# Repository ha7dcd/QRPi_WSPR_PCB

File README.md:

# QRPi – Whispering Raspberries: a Raspberry Pi QRP TX shield (20 m WSPR)

QRPi is a 20 m band, 20 dBm RF signal conditioner shield for the Raspberry Pi. It takes the RF square wave that the Pi generates on a GPIO pin and turns it into a clean, filtered QRP transmit signal: a MOSFET (MMBF170) stage followed by a multi-section low-pass filter. It was presented as a TAPR-DCC 2015 talk paper and was sold through TAPR and on Amazon.

This repository holds the board's original EAGLE design and manufacturing files (rev 1.6), and a KiCad 10 version of the same design.

*An earlier prototype (rev 1.1) on a Raspberry Pi model B, with a coax pigtail on the antenna terminal.*

## About the project (from [rfsparkling.com/qrpi](https://rfsparkling.com/qrpi/))

**QRPi - A Raspberry Pi QRP TX Shield Design, TAPR-DCC Talk paper 2015** ([PDF in this repo](docs/DCC2015-QRPI-HA7DCD.pdf))

QRPi is an RF signal conditioner shield for Raspberry Pi. Sourcing the RaspberryPi generated RF signal from GPIO4.

Right now existing only for the **20m band** for **14.0971 MHz** Later on will designed for other bands as well (10m in prototype).

In default GPIO4 mode can be used with [WsprryPi](https://github.com/JamesP6000/WsprryPi), [SSTV](https://github.com/JennyList/LanguageSpy/tree/master/RaspberryPi/rf/sstv), [CW](https://github.com/JamesP6000/PiCW), check manual here: [j.mp/tapr-qrpi](http://j.mp/tapr-qrpi) GPIO4 mode works with RPi 1 B, B+ and RPi 2 as well for WSPR mode.
When using in the **experimental GPIO18** mode (solder jumper selectable; SSB USB, LSB, NFM, WFM, AM with [qtcsdr](https://github.com/ha7ilm/qtcsdr) and [rpitx](https://github.com/F5OEO/rpitx)) it works only with RPi 2 right now (due to CPU demand)

However please be aware that QRPi was engineered and tested for GPIO4 pin, using WSPR modulation!
I'm adding GPIO18 option for **experimental mode only** to use with [qtcsdr](https://github.com/ha7ilm/qtcsdr) and [rpitx](https://github.com/F5OEO/rpitx)! By default the solder jumper is set for GPIO4 by short cut. As for VFO operation (CW signal) GPIO18 works nice but not yet tested comprehensively for other modulation yet, **please take care of this** in shake of RF spectrum emission! The QRPi shield is available at TAPR's webshop: <https://www.tapr.org/kits_20M-wspr-pi.html>

Now available at Amazon too: <https://www.amazon.com/Raspberry-QRP-Sheild-WSPR-Meters/dp/B01FWFKN40/>

Thanks for your interest!

73,
HA7DCD

Video: <https://www.youtube.com/watch?v=w-OTpw2Ai0k>

## The board in 3D (KiCad 10)

| Top | Bottom |
|---|---|
|  |  |

Two-layer board. The Raspberry Pi GPIO header pins pass through the board and into a 2x7 SMD female socket on the top side. The antenna is connected to a 2-pole Phoenix MPT 0,5/2-2,54 screw terminal. The GPIO4 / GPIO18 drive is selected on the bottom side: GPIO4 is shorted by default.

## Repository contents

| Path | What it is |
|---|---|
| `Eagle/20m_QRPi_1V6.sch`, `Eagle/20m_QRPi_1V6.brd` | Original EAGLE schematic and board (EAGLE 6.4 XML format) |
| `Eagle/20m_QRPi_1V6_sch.pdf`, `_top.pdf`, `_bot.pdf` | Schematic and board prints |
| `Eagle/20m_RPI_WSPR_TX_BOM_SMDmount.xlsx` | Bill of materials (SMD assembly) |
| `Eagle/CAM/20m_RPI_WSPR_TX_1v6.zip` | Original manufacturing files: Gerbers, Excellon drill files, PDFs |
| `KiCad/` | KiCad 10 project: schematic, PCB, project symbol and footprint libraries, design rules |
| `KiCad/3dmodels/` | STEP models used by the 3D view, from the KiCad standard library |
| `docs/` | TAPR-DCC 2015 paper, prototype photo, 3D renders, banner |

## About the KiCad version

The KiCad project was converted from the EAGLE files with [Eagle Exhumer](https://github.com/z2labs/eagle-exhumer) and then checked against the EAGLE source and the original manufacturing files:

- Netlist of the schematic and of the board: identical to EAGLE (no shorts, no opens, no renamed nets)
- 33 parts, 78 pads, 169 holes, 144 vias: same position, side, rotation, value, size and drill as in EAGLE
- KiCad-generated Gerbers and drill files compared with the original EAGLE manufacturing files: copper (outside the polygon pours), solder mask, paste and all 169 drill holes match. Polygon pour fill differs by about 2.5 % because EAGLE and KiCad use different fill algorithms.
- Remaining DRC items are the same ones the original EAGLE design carries: the JP1 GPIO4/GPIO18 jumper's solder-mask opening intentionally exposes the GPIO4 track and ground.

Only the EAGLE drawing frame was removed (KiCad draws its own page frame). 3D models were added for 30 of 33 footprints; the solder jumpers JP1 and SJ1 and the OSHW logo have none.

## License

Copyright 2015 Zoltan Doczi - HA7DCD. The hardware design is licensed under the TAPR Open Hardware License (<http://tapr.org/OHL>).

The STEP models in `KiCad/3dmodels/` come from the KiCad library (CC-BY-SA 4.0 with an exception that allows their use in designs, see <https://www.kicad.org/libraries/license/>).

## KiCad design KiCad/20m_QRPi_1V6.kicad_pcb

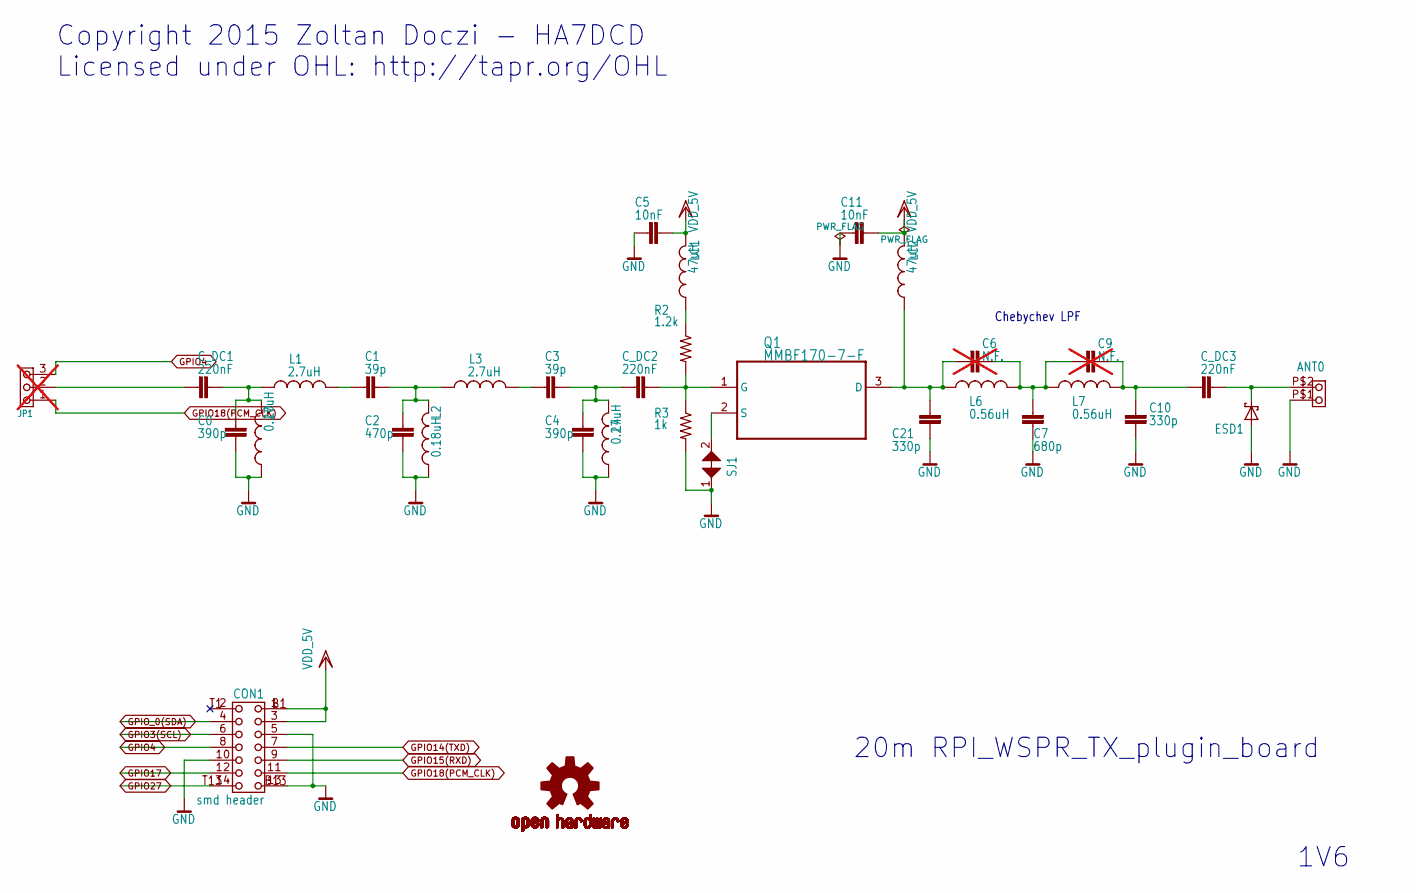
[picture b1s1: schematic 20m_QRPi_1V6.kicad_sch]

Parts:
ANT0: TERMINAL_WIRE_2P_17256562P; WIRE_CONTACT_2P
C0, C4: 390p; 0603
C1, C3: 39p; 0603
C2: 470p; 0603
C5, C11: 10nF; 0603
C6, C9: N.F.; 0603; not fitted
C7: 680p; 0603
C10, C21: 330p; 0603
CON1: smd header; 2X7-SMT_CROSSPCB_ASSYM_DUMY26HOLES
C_DC1, C_DC2, C_DC3: 220nF; 0603
ESD1: PGB1010603NRHF; 0603__v2
JP1: N.F.; PIN3-B_SHORT23; not fitted
L0, L4: 0.27uH; L1210
L1, L3: 2.7uH; L1210
L2: 0.18uH; L1210
L6, L7: 0.56uH; L1210
LC1, LC2: 47uH; L1210
Q1: MMBF170-7-F; SOT103P240X110-3N
R2: 1.2k; R0402
R3: 1k; R0402
SJ1: JUMPER_SMD_MICRO_SHORT
U$15: OSHW-LOGOS; OSHW-LOGO-S

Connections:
GND: ANT0.P$1 (A), C0.1, C2.1, C4.1, C5.2, C7.1, C10.1, C11.2, C21.1, CON1.5, CON1.10, CON1.13, ESD1.1 (A), L0.1, L2.1, L4.1, R3.2, SJ1.1
GPIO3(SCL): CON1.6
GPIO4: CON1.8, JP1.3
GPIO14(TXD): CON1.7
GPIO15(RXD): CON1.9
GPIO17: CON1.12
GPIO18(PCM_CLK): CON1.11, JP1.1
GPIO27: CON1.14
GPIO_0(SDA): CON1.4
unnamed: ANT0.P$2 (B), C_DC3.1, ESD1.2 (C)
unnamed: C0.2, C_DC1.1, L0.2, L1.1
unnamed: C1.1, C2.2, L2.2, L3.1
unnamed: C1.2, L1.2
unnamed: C3.1, C4.2, C_DC2.2, L4.2
unnamed: C3.2, L3.2
unnamed: C6.1, C7.2, C9.2, L6.2, L7.1
unnamed: C9.1, C10.2, C_DC3.2, L7.2
unnamed: C_DC1.2, JP1.2
unnamed: LC1.1, R2.1
unnamed: C6.2, C21.2, L6.1, LC2.1, Q1.3 (D)
unnamed: C_DC2.1, Q1.1 (G), R2.2, R3.1
unnamed: Q1.2 (S), SJ1.2
VDD_5V: C5.1, C11.1, CON1.1, CON1.3, LC1.2, LC2.2

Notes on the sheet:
20m RPI_WSPR_TX_plugin_board
Chebychev LPF
Copyright 2015 Zoltan Doczi - HA7DCD Licensed under OHL: http://tapr.org/OHL
1V6

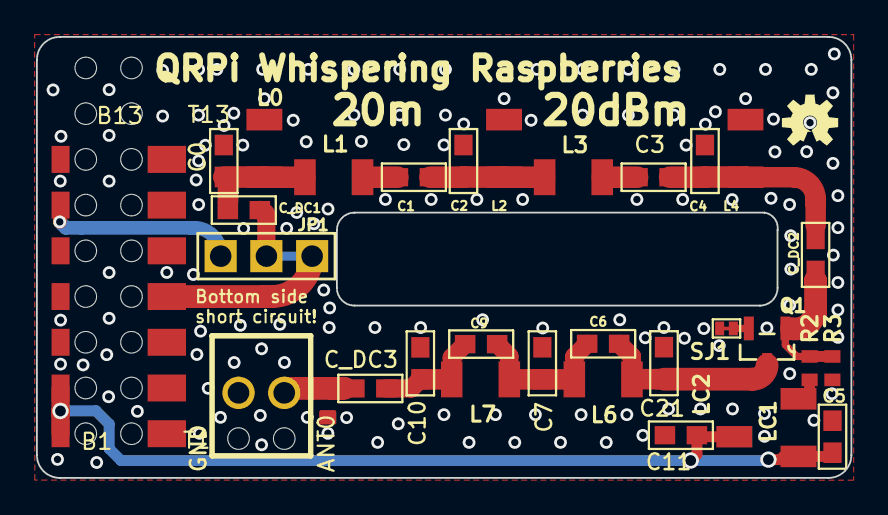
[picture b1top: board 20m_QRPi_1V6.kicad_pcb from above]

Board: 2 copper layers, 45.2 x 24.5 mm, 33 parts (0 on the bottom side), 17 nets.

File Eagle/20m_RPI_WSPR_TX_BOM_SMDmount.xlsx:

| BOM Version 1V1
Qty | Value | Newark website link | Device | Package | Parts | Description | DESCR | DISTRI | DISTRINR | MANUF | MANUFNR | MPN | OC_FARNELL | OC_NEWARK | PACKAGE | SUPPLIER | VENDOR
1 | 0.18uH | http://www.newark.com/taiyo-yuden/lbm2016tr18j/inductor-180n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 | INDUCTOR_L_1210 | L1210 | L2 |  | Inductor, wirewound |  |  | TDK | NLCV32 series
2 | 0.27uH | http://www.newark.com/taiyo-yuden/brl3225tr27m/inductor-270n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 | INDUCTOR_L_1210 | L1210 | L0, L4 |  | Inductor, wirewound |  |  | TDK | NLCV32 series
2 | 0.56uH | http://www.newark.com/tdk/nlv32t-r56j-pf/signal-line-ind-56n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 | INDUCTOR_L_1210 | L1210 | L6, L7 |  | Inductor, wirewound |  |  | TDK | NLCV32 series
1 | 1.2k | http://www.newark.com/yageo/rc0402jr-071k2l/thick-film-resis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 | R-US_R0402 | R0402 | R2 | RESISTOR, American symbol
2 | 10nF | http://www.newark.com/multicomp/mc0603b103m500ct/ceramic-cap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 | CAP-SMD0603 | 0603 | C5, C11
1 | 1k | http://www.newark.com/yageo/rc0402jr-131kl/thick-film-resist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 | R-US_R0402 | R0402 | R3 | RESISTOR, American symbol
2 | 2.7uH | http://www.newark.com/taiyo-yuden/lbm2016t2r7j/inductor-2-7u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 | INDUCTOR_L_1210 | L1210 | L1, L3 |  | Inductor, wirewound |  |  | TDK | NLCV32 series
3 | 220nF | http://www.newark.com/multicomp/mc0603f224z160ct/ceramic-cap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 | CAP-SMD0603 | 0603 | C_DC1, C_DC2, C_DC3
2 | 330p | http://www.newark.com/multicomp/mc0603b331k500ct/ceramic-cap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 | CAP-SMD0603 | 0603 | C10, C21
2 | 390p | http://www.newark.com/tdk/c1608c0g1h391j080aa/ceramic-capaci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 | CAP-SMD0603 | 0603 | C0, C4
2 | 39p | http://www.newark.com/multicomp/mc0603n390j500ct/ceramic-cap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 | CAP-SMD0603 | 0603 | C1, C3
1 | 470p | http://www.newark.com/multicomp/mc0603b471k101ct/ceramic-cap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 | CAP-SMD0603 | 0603 | C2
2 | 47uH | http://www.newark.com/tdk/nlcv32t-470k-pf/power-line-ind-47u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 | INDUCTOR_L_1210 | L1210 | LC1, LC2 |  | Inductor, wirewound |  |  | TDK | NLCV32 series
1 | 680p | http://www.newark.com/multicomp/mc0603b681k500ct/ceramic-cap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 | CAP-SMD0603 | 0603 | C7
1 | MMBF170-7-F | http://www.newark.com/fairchild-semiconductor/mmbf170/mosfet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 | MMBF170-7-F | SOT103P240X110-3N | Q1 | N-CHANNEL ENHANCEMENT MODE FIELD EFFECT TRANSISTOR |  |  |  |  |  | MMBF170-7-F | 1773582 | 51R6804 | SOT-23-3 | DIODES INC.
2 | N.F. |  | CAP-SMD0603 | 0603 | C6, C9
1 | PGB1010603NRHF Optional! | http://www.newark.com/littelfuse/pgb1010603nr/tvs-diode-24v-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 | SMF33A-GS08_ESD0603 | 0603 | ESD1
1 | TERMINAL_WIRE_2P_17256562P | http://www.newark.com/phoenix-contact/1725656/terminal-block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 | TERMINAL_WIRE_2P_17256562P | WIRE_CONTACT_2P | ANT | PHOENIX CONTACT 1725656 TERMINAL BLOCK, WIRE TO BRD, 2POS, 20AWG |  | Farnell | 3041359 |  |  |  |  |  |  |  | Phonix
1 | smd header | http://www.newark.com/global-connector-technology/bg120-10-a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 | PINHD-2X7_SMD2X7_CROSSPCB_ASSYM_DUMMY26PIN | 2X7-SMT_CROSSPCB_ASSYM_DUMY26HOLES | CON1 |  | RECEPTACLE, BOARD TO BOARD, 2ROW, 10WAY | Farnell | 2293771 | GLOBAL CONNECTOR TECHNOLOGY | BG120-10-A-0-N-D
 | Yellow marking means = | Not available in the requried size, just smaller footprint. Should fit and sold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
